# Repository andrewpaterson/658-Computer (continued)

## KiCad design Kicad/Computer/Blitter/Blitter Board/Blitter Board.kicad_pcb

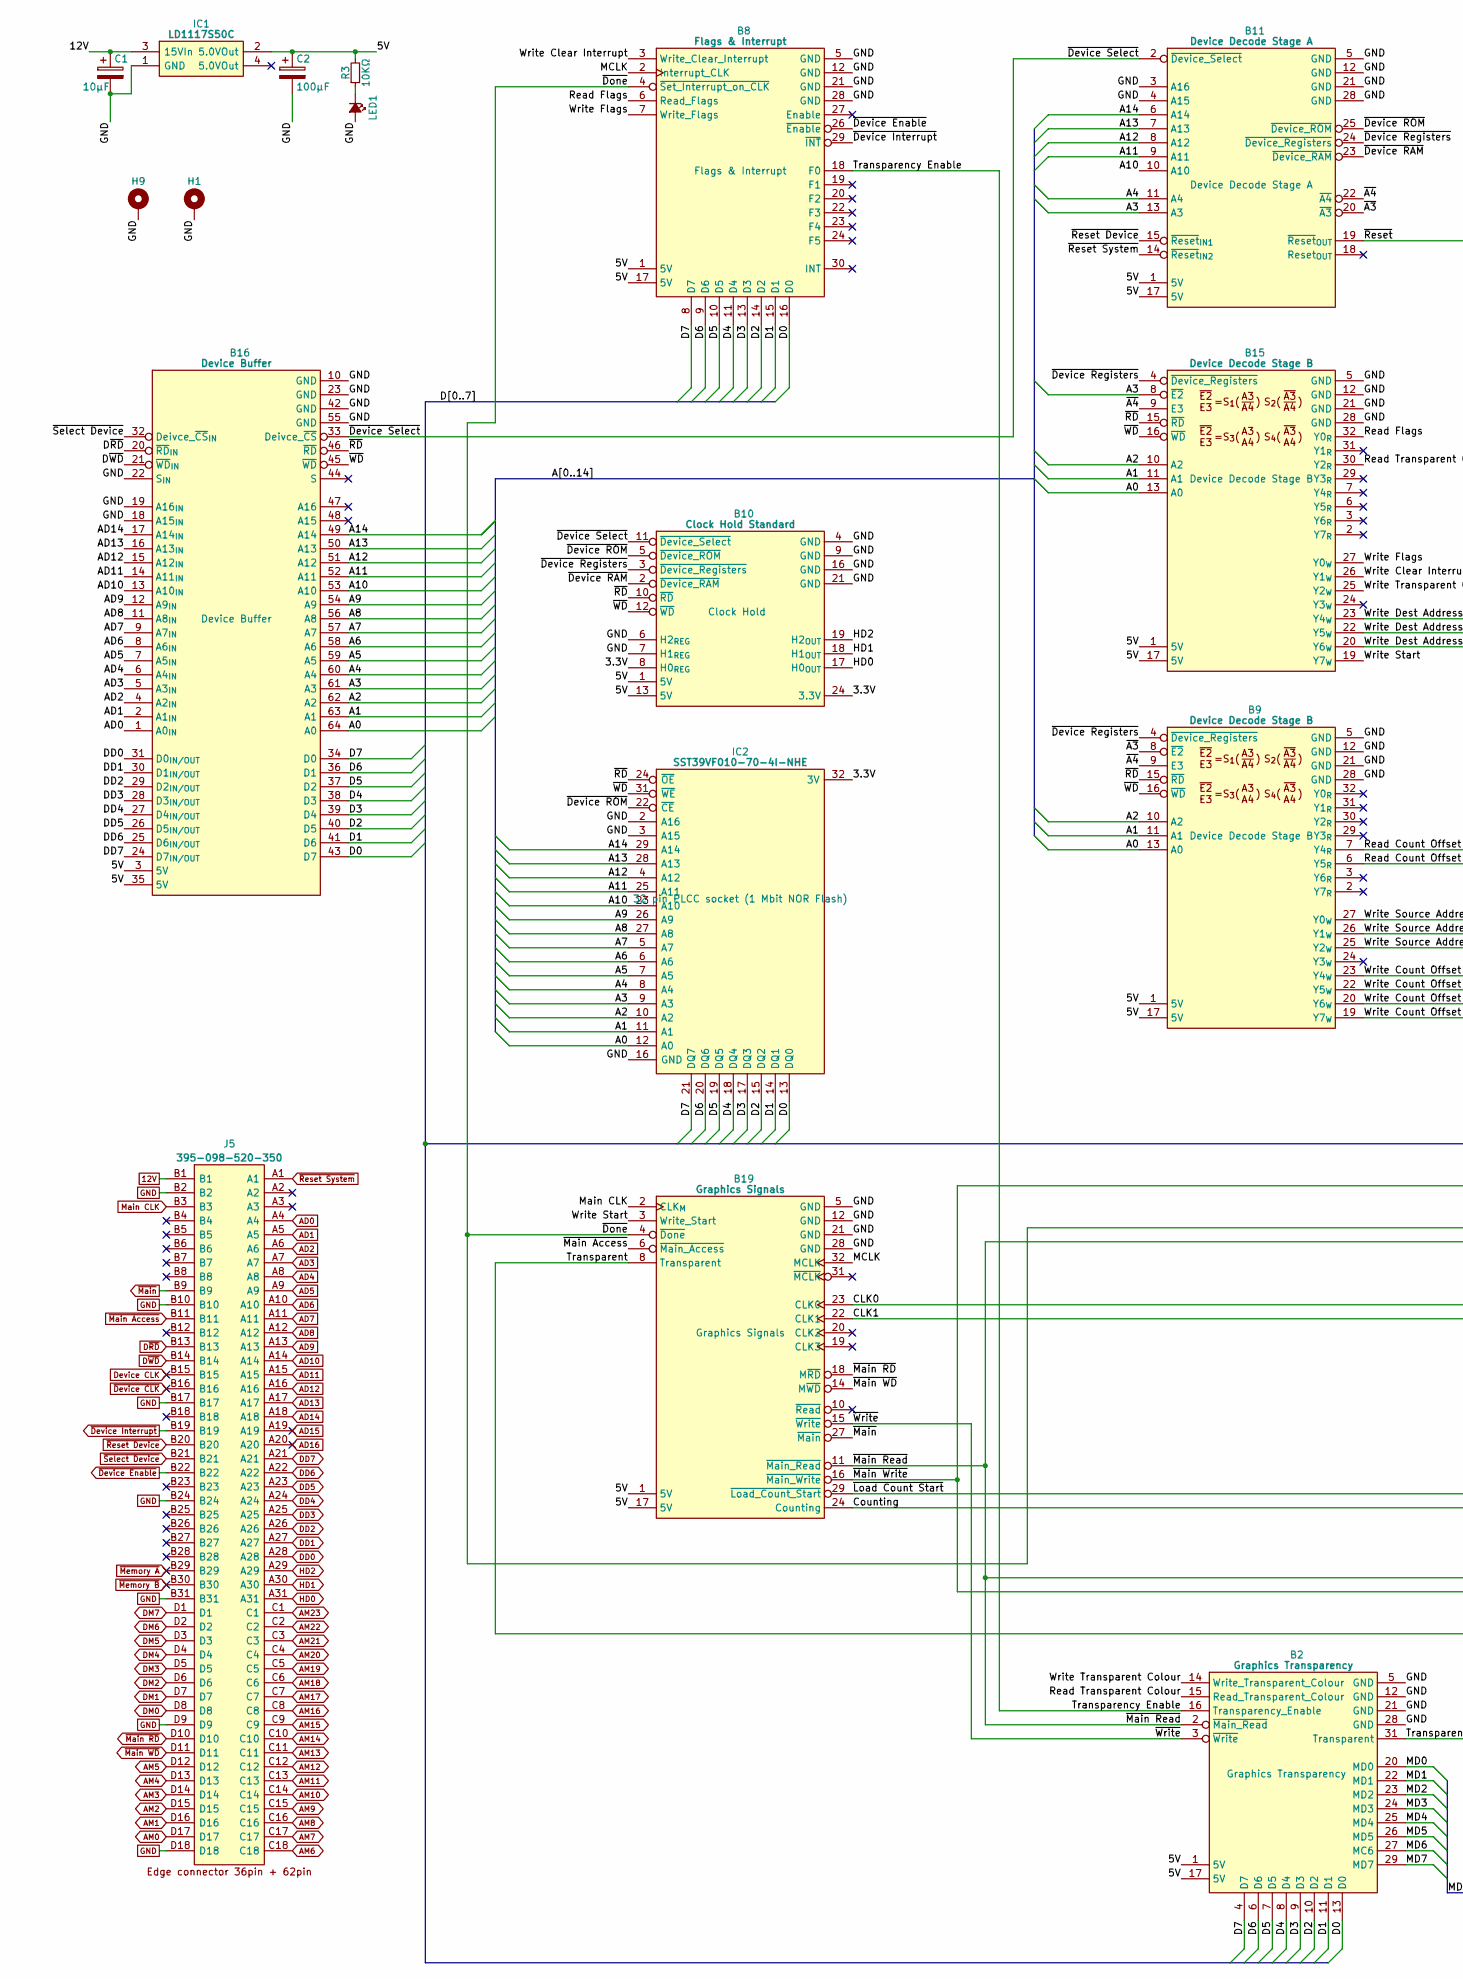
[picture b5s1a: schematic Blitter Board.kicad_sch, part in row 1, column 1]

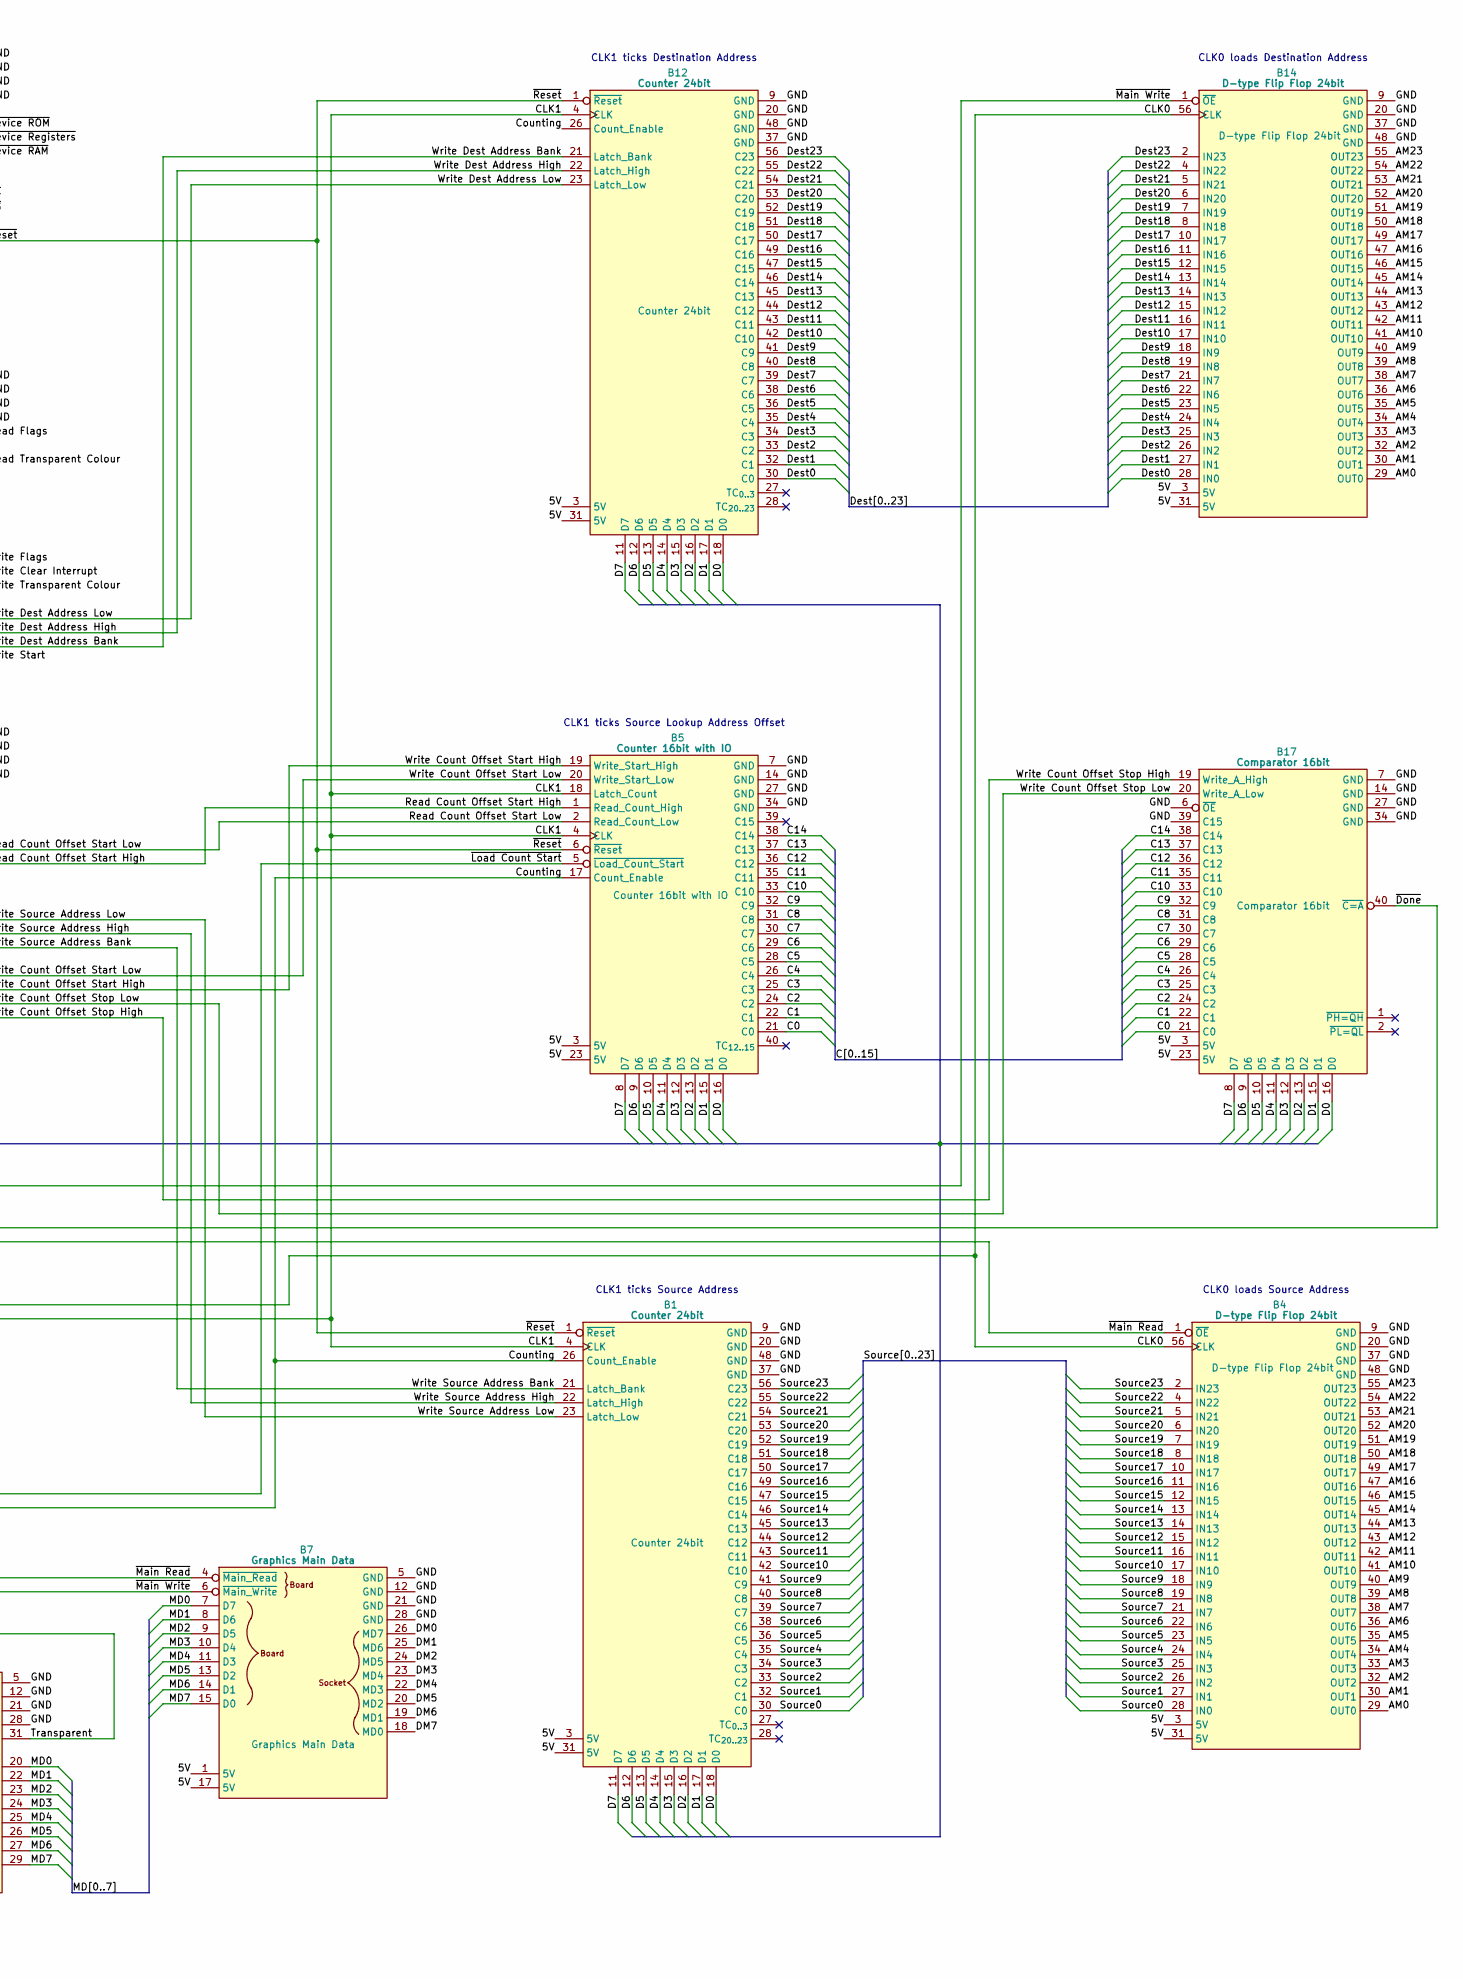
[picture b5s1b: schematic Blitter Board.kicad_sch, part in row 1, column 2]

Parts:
B1, B12: Counter 24bit; HCP65_Counter_24bit
B2: Graphics Transparency; HCP65_Graphics_Transparency
B4, B14: D-type Flip Flop 24bit; HCP65_D_Flip_Flop_24bit
B5: Counter 16bit with IO; HCP65_Counter_16bit_DIO
B7: Graphics Main Data; HCP65_Graphics_Main_Data
B8: Flags & Interrupt; HCP65_Flags_Interrupt
B9, B15: Device Decode Stage B; HCP65_Device_Decode_Stage_B
B10: Clock Hold Standard; HCP65_Clock_Hold_Standard
B11: Device Decode Stage A; HCP65_Device_Decode_Stage_A
B16: Device Buffer; HCP65_Device_Buffer
B17: Comparator 16bit; HCP65_Comparator_16bit
B19: Graphics Signals; HCP65_Graphics_Signals
C1: 10μF; CP_Radial_D4.0mm_P2.00mm
C2: 100μF; CP_Radial_D4.0mm_P2.00mm
H1, H9: MountingHole_Pad; HCP65_MountingHole_M3_
IC1: LD1117S50C; LD1117S33C; Manufacturer_Part_Number LD1117S50C
IC2: SST39VF010-70-4I-NHE; 5408803224008; Manufacturer_Part_Number SST39VF010-70-4I-NHE
J5: 395-098-520-350; 98pin Edge Connector; Manufacturer_Part_Number 395-098-520-350; Mouser Part Number 587-395-098-520-350
LED1: LED; LED_D5.0mm
R3: 10KΩ; R_0805

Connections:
12V: C1.1, IC1.3 (15VIn), J5.B1
/3.3V: B10.8 (H0_{REG}), B10.24 (3.3V), IC2.32 (3V)
/5V: B1.3 (5V), B1.31 (5V), B2.1 (5V), B2.17 (5V), B4.3 (5V), B4.31 (5V), B5.3 (5V), B5.23 (5V), B7.1 (5V), B7.17 (5V), B8.1 (5V), B8.17 (5V), B9.1 (5V), B9.17 (5V), B10.1 (5V), B10.13 (5V), B11.1 (5V), B11.17 (5V), B12.3 (5V), B12.31 (5V), B14.3 (5V), B14.31 (5V), B15.1 (5V), B15.17 (5V), B16.3 (5V), B16.35 (5V), B17.3 (5V), B17.23 (5V), B19.1 (5V), B19.17 (5V), C2.1, IC1.2 (5.0VOut), R3.2
/A0: B9.13 (A0), B15.13 (A0), B16.64 (A0), IC2.12 (A0)
/A1: B9.11 (A1), B15.11 (A1), B16.63 (A1), IC2.11 (A1)
/A2: B9.10 (A2), B15.10 (A2), B16.62 (A2), IC2.10 (A2)
/A3: B11.13 (A3), B15.8 (~E2), B16.61 (A3), IC2.9 (A3)
/A4: B11.11 (A4), B16.60 (A4), IC2.8 (A4)
/A5: B16.59 (A5), IC2.7 (A5)
/A6: B16.58 (A6), IC2.6 (A6)
/A7: B16.57 (A7), IC2.5 (A7)
/A8: B16.56 (A8), IC2.27 (A8)
/A9: B16.54 (A9), IC2.26 (A9)
/A10: B11.10 (A10), B16.53 (A10), IC2.23 (A10)
/A11: B11.9 (A11), B16.52 (A11), IC2.25 (A11)
/A12: B11.8 (A12), B16.51 (A12), IC2.4 (A12)
/A13: B11.7 (A13), B16.50 (A13), IC2.28 (A13)
/A14: B11.6 (A14), B16.49 (A14), IC2.29 (A14)
/C0: B5.21 (C0), B17.21 (C0)
/C1: B5.22 (C1), B17.22 (C1)
/C2: B5.24 (C2), B17.24 (C2)
/C3: B5.25 (C3), B17.25 (C3)
/C4: B5.26 (C4), B17.26 (C4)
/C5: B5.28 (C5), B17.28 (C5)
/C6: B5.29 (C6), B17.29 (C6)
/C7: B5.30 (C7), B17.30 (C7)
/C8: B5.31 (C8), B17.31 (C8)
/C9: B5.32 (C9), B17.32 (C9)
/C10: B5.33 (C10), B17.33 (C10)
/C11: B5.35 (C11), B17.35 (C11)
/C12: B5.36 (C12), B17.36 (C12)
/C13: B5.37 (C13), B17.37 (C13)
/C14: B5.38 (C14), B17.38 (C14)
/CLK0: B4.56 (CLK), B14.56 (CLK), B19.23 (CLK0)
/CLK1: B1.4 (CLK), B5.4 (CLK), B5.18 (Latch_Count), B12.4 (CLK), B19.22 (CLK1)
/Counting: B1.26 (Count_Enable), B5.17 (Count_Enable), B12.26 (Count_Enable), B19.24 (Counting)
/D0: B1.18 (D0), B2.13 (D0), B5.16 (D0), B8.16 (D0), B12.18 (D0), B16.43 (D7), B17.16 (D0), IC2.13 (DQ0)
/D1: B1.17 (D1), B2.11 (D1), B5.15 (D1), B8.15 (D1), B12.17 (D1), B16.41 (D6), B17.15 (D1), IC2.14 (DQ1)
/D2: B1.16 (D2), B2.10 (D2), B5.13 (D2), B8.14 (D2), B12.16 (D2), B16.40 (D5), B17.13 (D2), IC2.15 (DQ2)
/D3: B1.15 (D3), B2.9 (D3), B5.12 (D3), B8.13 (D3), B12.15 (D3), B16.39 (D4), B17.12 (D3), IC2.17 (DQ3)
/D4: B1.14 (D4), B2.8 (D4), B5.11 (D4), B8.11 (D4), B12.14 (D4), B16.38 (D3), B17.11 (D4), IC2.18 (DQ4)
/D5: B1.13 (D5), B2.7 (D5), B5.10 (D5), B8.10 (D5), B12.13 (D5), B16.37 (D2), B17.10 (D5), IC2.19 (DQ5)
/D6: B1.12 (D6), B2.6 (D6), B5.9 (D6), B8.9 (D6), B12.12 (D6), B16.36 (D1), B17.9 (D6), IC2.20 (DQ6)
/D7: B1.11 (D7), B2.4 (D7), B5.8 (D7), B8.8 (D7), B12.11 (D7), B16.34 (D0), B17.8 (D7), IC2.21 (DQ7)
/Dest0: B12.30 (C0), B14.28 (IN0)
/Dest1: B12.32 (C1), B14.27 (IN1)
/Dest2: B12.33 (C2), B14.26 (IN2)
/Dest3: B12.34 (C3), B14.25 (IN3)
/Dest4: B12.35 (C4), B14.24 (IN4)
/Dest5: B12.36 (C5), B14.23 (IN5)
/Dest6: B12.38 (C6), B14.22 (IN6)
/Dest7: B12.39 (C7), B14.21 (IN7)
/Dest8: B12.40 (C8), B14.19 (IN8)
/Dest9: B12.41 (C9), B14.18 (IN9)
/Dest10: B12.42 (C10), B14.17 (IN10)
/Dest11: B12.43 (C11), B14.16 (IN11)
/Dest12: B12.44 (C12), B14.15 (IN12)
/Dest13: B12.45 (C13), B14.14 (IN13)
/Dest14: B12.46 (C14), B14.13 (IN14)
/Dest15: B12.47 (C15), B14.12 (IN15)
/Dest16: B12.49 (C16), B14.11 (IN16)
/Dest17: B12.50 (C17), B14.10 (IN17)
/Dest18: B12.51 (C18), B14.8 (IN18)
/Dest19: B12.52 (C19), B14.7 (IN19)
/Dest20: B12.53 (C20), B14.6 (IN20)
/Dest21: B12.54 (C21), B14.5 (IN21)
/Dest22: B12.55 (C22), B14.4 (IN22)
/Dest23: B12.56 (C23), B14.2 (IN23)
/MCLK: B8.2 (Interrupt_CLK), B19.32 (MCLK)
/MD0: B2.20 (MD0), B7.7 (D7)
/MD1: B2.22 (MD1), B7.8 (D6)
/MD2: B2.23 (MD2), B7.9 (D5)
/MD3: B2.24 (MD3), B7.10 (D4)
/MD4: B2.25 (MD4), B7.11 (D3)
/MD5: B2.26 (MD5), B7.13 (D2)
/MD6: B2.27 (MC6), B7.14 (D1)
/MD7: B2.29 (MD7), B7.15 (D0)
/Read Count Offset Start High: B5.1 (Read_Count_High), B9.6 (Y5_{R})
/Read Count Offset Start Low: B5.2 (Read_Count_Low), B9.7 (Y4_{R})
/Read Flags: B8.6 (Read_Flags), B15.32 (Y0_{R})
/Read Transparent Colour: B2.15 (Read_Transparent_Colour), B15.30 (Y2_{R})
/Source0: B1.30 (C0), B4.28 (IN0)
/Source1: B1.32 (C1), B4.27 (IN1)
/Source2: B1.33 (C2), B4.26 (IN2)
/Source3: B1.34 (C3), B4.25 (IN3)
/Source4: B1.35 (C4), B4.24 (IN4)
/Source5: B1.36 (C5), B4.23 (IN5)
/Source6: B1.38 (C6), B4.22 (IN6)
/Source7: B1.39 (C7), B4.21 (IN7)
/Source8: B1.40 (C8), B4.19 (IN8)
/Source9: B1.41 (C9), B4.18 (IN9)
/Source10: B1.42 (C10), B4.17 (IN10)
/Source11: B1.43 (C11), B4.16 (IN11)
/Source12: B1.44 (C12), B4.15 (IN12)
/Source13: B1.45 (C13), B4.14 (IN13)
/Source14: B1.46 (C14), B4.13 (IN14)
/Source15: B1.47 (C15), B4.12 (IN15)
/Source16: B1.49 (C16), B4.11 (IN16)
/Source17: B1.50 (C17), B4.10 (IN17)
/Source18: B1.51 (C18), B4.8 (IN18)
/Source19: B1.52 (C19), B4.7 (IN19)
/Source20: B1.53 (C20), B4.6 (IN20)
/Source21: B1.54 (C21), B4.5 (IN21)
/Source22: B1.55 (C22), B4.4 (IN22)
/Source23: B1.56 (C23), B4.2 (IN23)
/Transparency Enable: B2.16 (Transparency_Enable), B8.18 (F0)
/Transparent: B2.31 (Transparent), B19.8 (Transparent)
/Write Clear Interrupt: B8.3 (Write_Clear_Interrupt), B15.26 (Y1_{W})
/Write Count Offset Start High: B5.19 (Write_Start_High), B9.22 (Y5_{W})
/Write Count Offset Start Low: B5.20 (Write_Start_Low), B9.23 (Y4_{W})
/Write Count Offset Stop High: B9.19 (Y7_{W}), B17.19 (Write_A_High)
/Write Count Offset Stop Low: B9.20 (Y6_{W}), B17.20 (Write_A_Low)
/Write Dest Address Bank: B12.21 (Latch_Bank), B15.20 (Y6_{W})
/Write Dest Address High: B12.22 (Latch_High), B15.22 (Y5_{W})
/Write Dest Address Low: B12.23 (Latch_Low), B15.23 (Y4_{W})
/Write Flags: B8.7 (Write_Flags), B15.27 (Y0_{W})
/Write Source Address Bank: B1.21 (Latch_Bank), B9.25 (Y2_{W})
/Write Source Address High: B1.22 (Latch_High), B9.26 (Y1_{W})
/Write Source Address Low: B1.23 (Latch_Low), B9.27 (Y0_{W})
/Write Start: B15.19 (Y7_{W}), B19.3 (Write_Start)
/Write Transparent Colour: B2.14 (Write_Transparent_Colour), B15.25 (Y2_{W})
/~A3: B9.8 (~E2), B11.20 (~A3)
/~A4: B9.9 (E3), B11.22 (~A4), B15.9 (E3)
/~Device RAM: B10.2 (~Device_RAM), B11.23 (~Device_RAM)
/~Device ROM: B10.5 (~Device_ROM), B11.25 (~Device_ROM), IC2.22 (~CE)
/~Device Registers: B9.4 (~Device_Registers), B10.3 (~Device_Registers), B11.24 (~Device_Registers), B15.4 (~Device_Registers)
/~Device Select: B10.11 (~Device_Select), B11.2 (~Device_Select), B16.33 (Deivce_~CS)
/~Done: B8.4 (~Set_Interrupt_on_CLK), B17.40 (~C=A), B19.4 (~Done)
/~Load Count Start: B5.5 (~Load_Count_Start), B19.29 (~Load_Count_Start)
/~Main Read: B2.2 (~Main_Read), B4.1 (~OE), B7.4 (~Main_Read), B19.11 (~Main_Read)
/~Main Write: B7.6 (~Main_Write), B14.1 (~OE), B19.16 (~Main_Write)
/~RD: B9.15 (~RD), B10.10 (~RD), B15.15 (~RD), B16.46 (~RD), IC2.24 (~OE)
/~Reset: B1.1 (~Reset), B5.6 (~Reset), B11.19 (~Reset_{OUT}), B12.1 (~Reset)
/~WD: B9.16 (~WD), B10.12 (~WD), B15.16 (~WD), B16.45 (~WD), IC2.31 (~WE)
/~Write: B2.3 (~Write), B19.15 (~Write)
AD0: B16.1 (A0_{IN}), J5.A4
AD1: B16.2 (A1_{IN}), J5.A5
AD2: B16.4 (A2_{IN}), J5.A6
AD3: B16.5 (A3_{IN}), J5.A7
AD4: B16.6 (A4_{IN}), J5.A8
AD5: B16.7 (A5_{IN}), J5.A9
AD6: B16.8 (A6_{IN}), J5.A10
AD7: B16.9 (A7_{IN}), J5.A11
AD8: B16.11 (A8_{IN}), J5.A12
AD9: B16.12 (A9_{IN}), J5.A13
AD10: B16.13 (A10_{IN}), J5.A14
AD11: B16.14 (A11_{IN}), J5.A15
AD12: B16.15 (A12_{IN}), J5.A16
AD13: B16.16 (A13_{IN}), J5.A17
AD14: B16.17 (A14_{IN}), J5.A18
AD15: J5.A19
AD16: J5.A20
AM0: B4.29 (OUT0), B14.29 (OUT0), J5.D17
AM1: B4.30 (OUT1), B14.30 (OUT1), J5.D16
AM2: B4.32 (OUT2), B14.32 (OUT2), J5.D15
AM3: B4.33 (OUT3), B14.33 (OUT3), J5.D14
AM4: B4.34 (OUT4), B14.34 (OUT4), J5.D13
AM5: B4.35 (OUT5), B14.35 (OUT5), J5.D12
AM6: B4.36 (OUT6), B14.36 (OUT6), J5.C18
AM7: B4.38 (OUT7), B14.38 (OUT7), J5.C17
AM8: B4.39 (OUT8), B14.39 (OUT8), J5.C16
AM9: B4.40 (OUT9), B14.40 (OUT9), J5.C15
AM10: B4.41 (OUT10), B14.41 (OUT10), J5.C14
AM11: B4.42 (OUT11), B14.42 (OUT11), J5.C13
AM12: B4.43 (OUT12), B14.43 (OUT12), J5.C12
AM13: B4.44 (OUT13), B14.44 (OUT13), J5.C11
AM14: B4.45 (OUT14), B14.45 (OUT14), J5.C10
AM15: B4.46 (OUT15), B14.46 (OUT15), J5.C9
AM16: B4.47 (OUT16), B14.47 (OUT16), J5.C8
AM17: B4.49 (OUT17), B14.49 (OUT17), J5.C7
AM18: B4.50 (OUT18), B14.50 (OUT18), J5.C6
AM19: B4.51 (OUT19), B14.51 (OUT19), J5.C5
AM20: B4.52 (OUT20), B14.52 (OUT20), J5.C4
AM21: B4.53 (OUT21), B14.53 (OUT21), J5.C3
AM22: B4.54 (OUT22), B14.54 (OUT22), J5.C2
AM23: B4.55 (OUT23), B14.55 (OUT23), J5.C1
DD0: B16.31 (D0_{IN/OUT}), J5.A28
DD1: B16.30 (D1_{IN/OUT}), J5.A27
DD2: B16.29 (D2_{IN/OUT}), J5.A26
DD3: B16.28 (D3_{IN/OUT}), J5.A25
DD4: B16.27 (D4_{IN/OUT}), J5.A24
DD5: B16.26 (D5_{IN/OUT}), J5.A23
DD6: B16.25 (D6_{IN/OUT}), J5.A22
DD7: B16.24 (D7_{IN/OUT}), J5.A21
DM0: B7.26 (MD7), J5.D8
DM1: B7.25 (MD6), J5.D7
DM2: B7.24 (MD5), J5.D6
DM3: B7.23 (MD4), J5.D5
DM4: B7.22 (MD3), J5.D4
DM5: B7.20 (MD2), J5.D3
DM6: B7.19 (MD1), J5.D2
DM7: B7.18 (MD0), J5.D1
Device CLK: J5.B15
D~RD: B16.20 (~RD_{IN}), J5.B13
D~WD: B16.21 (~WD_{IN}), J5.B14
GND: B1.9 (GND), B1.20 (GND), B1.37 (GND), B1.48 (GND), B2.5 (GND), B2.12 (GND), B2.21 (GND), B2.28 (GND), B4.9 (GND), B4.20 (GND), B4.37 (GND), B4.48 (GND), B5.7 (GND), B5.14 (GND), B5.27 (GND), B5.34 (GND), B7.5 (GND), B7.12 (GND), B7.21 (GND), B7.28 (GND), B8.5 (GND), B8.12 (GND), B8.21 (GND), B8.28 (GND), B9.5 (GND), B9.12 (GND), B9.21 (GND), B9.28 (GND), B10.4 (GND), B10.6 (H2_{REG}), B10.7 (H1_{REG}), B10.9 (GND), B10.16 (GND), B10.21 (GND), B11.3 (A16), B11.4 (A15), B11.5 (GND), B11.12 (GND), B11.21 (GND), B11.28 (GND), B12.9 (GND), B12.20 (GND), B12.37 (GND), B12.48 (GND), B14.9 (GND), B14.20 (GND), B14.37 (GND), B14.48 (GND), B15.5 (GND), B15.12 (GND), B15.21 (GND), B15.28 (GND), B16.10 (GND), B16.18 (A15_{IN}), B16.19 (A16_{IN}), B16.22 (S_{IN}), B16.23 (GND), B16.42 (GND), B16.55 (GND), B17.6 (~OE), B17.7 (GND), B17.14 (GND), B17.27 (GND), B17.34 (GND), B17.39 (C15), B19.5 (GND), B19.12 (GND), B19.21 (GND), B19.28 (GND), C1.2, C2.2, H1.1 (GND), H9.1 (GND), IC1.1 (GND), IC2.2 (A16), IC2.3 (A15), IC2.16 (GND), J5.B2, J5.B10, J5.B17, J5.B24, J5.B31, J5.D9, J5.D18, LED1.2 (A)
HD0: B10.17 (H0_{OUT}), J5.A31
HD1: B10.18 (H1_{OUT}), J5.A30
HD2: B10.19 (H2_{OUT}), J5.A29
Main CLK: B19.2 (CLK_{M}), J5.B3
unnamed: LED1.1 (K), R3.1
~Device CLK: J5.B16
~Device Enable: B8.26 (~Enable), J5.B22
~Device Interrupt: B8.29 (~INT), J5.B19
~Main Access: B19.6 (~Main_Access), J5.B11
~Main RD: B19.18 (M~RD), J5.D10
~Main WD: B19.14 (M~WD), J5.D11
~Main: B19.27 (~Main), J5.B9
~Memory A: J5.B29
~Memory B: J5.B30
~Reset Device: B11.15 (~Reset_{IN1}), J5.B20
~Reset System: B11.14 (~Reset_{IN2}), J5.A1
~Select Device: B16.32 (Deivce_~CS_{IN}), J5.B21

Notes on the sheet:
CLK1 ticks Source Lookup Address Offset
CLK0 loads Destination Address
CLK1 ticks Destination Address
CLK1 ticks Source Address
CLK0 loads Source Address

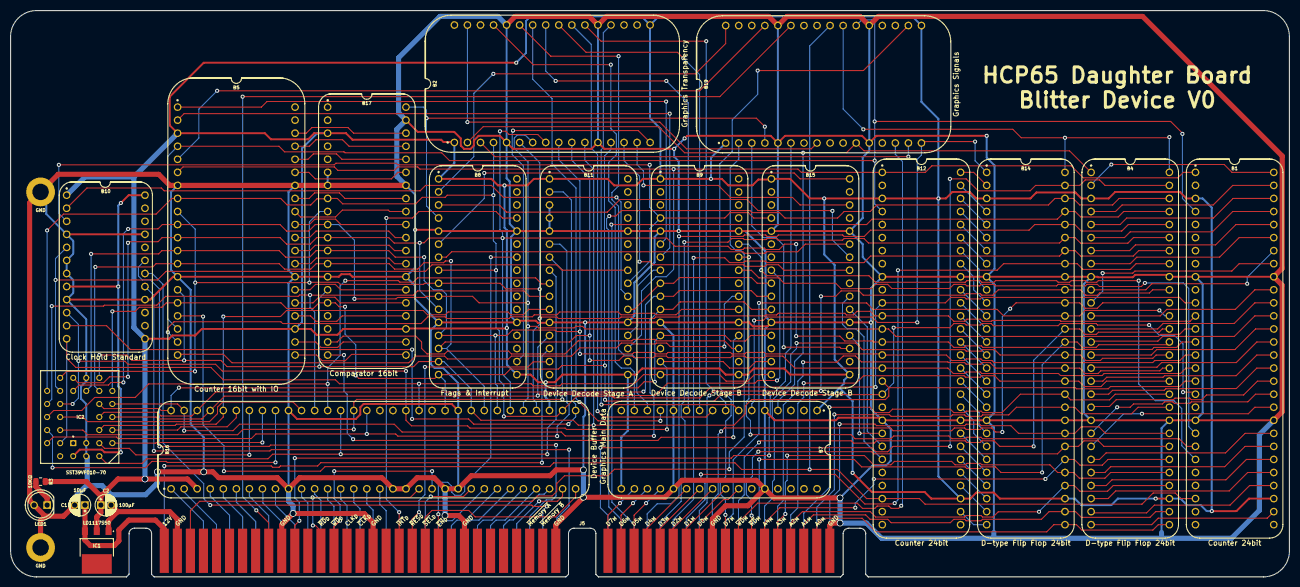
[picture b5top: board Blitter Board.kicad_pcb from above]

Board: 2 copper layers, 248.9 x 110.2 mm, 24 parts (0 on the bottom side), 207 nets.

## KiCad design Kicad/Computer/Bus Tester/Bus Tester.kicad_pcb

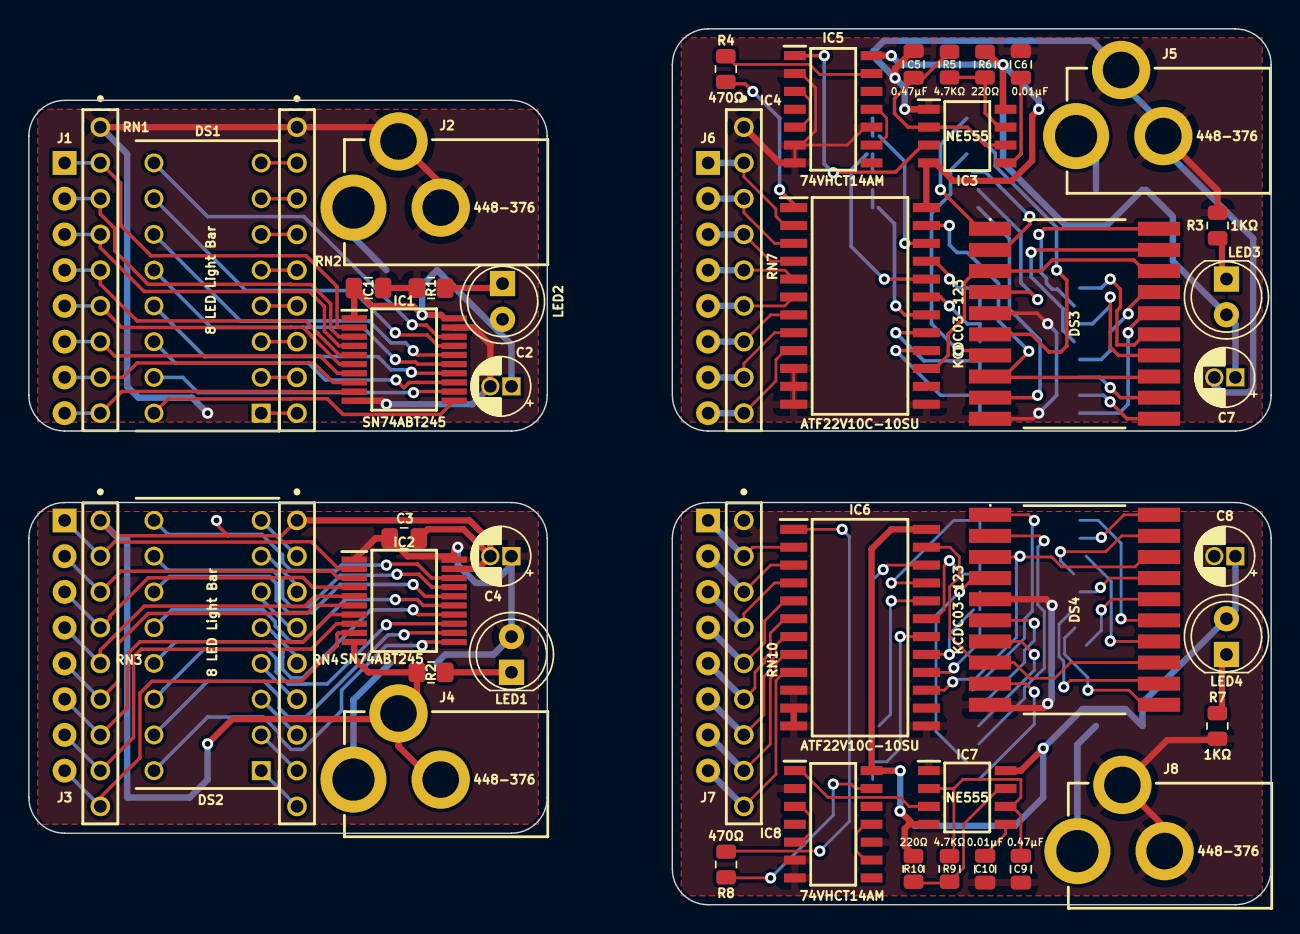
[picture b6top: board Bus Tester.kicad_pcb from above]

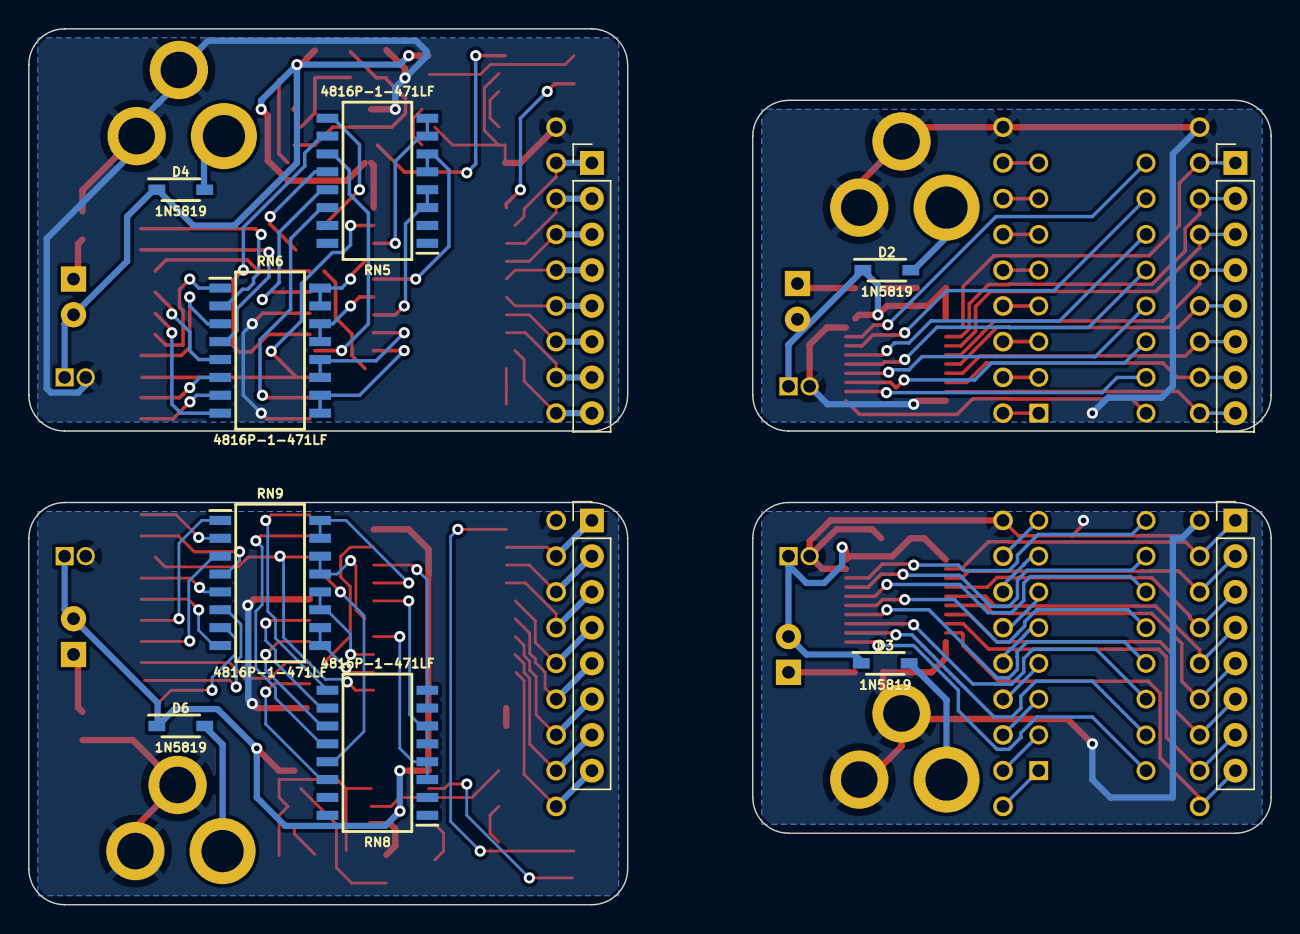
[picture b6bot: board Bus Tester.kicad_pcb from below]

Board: 2 copper layers, 88.3 x 62.2 mm, 58 parts (12 on the bottom side), 142 nets.

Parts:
C1, C3: C_Small; C_0805_2012Metric_Pad1.18x1.45mm_HandSolder
C2, C4, C7, C8: C_Polarized; CP_Radial_D4.0mm_P1.50mm
C5, C6, C9, C10: C_0805
D2, D3, D4, D6: 1N5819HW-7-F; SOD3716X145N
DS1, DS2: 8 LED Light Bar; DIP8LEDBAR
DS3, DS4: KCDC03-123; KCDC03123
IC1, IC2: SN74ABT245; SOP65P780X200-20N
IC3, IC7: NE555DRG4; SOIC127P600X175-8N
IC4, IC6: ATF22V10C-10SU; SOIC127P1032X265-24N
IC5, IC8: 74VHCT14AM; SOIC127P600X175-14N
J1, J3, J6, J7: Conn_01x08_Male; PinHeader_1x08_P2.54mm_Vertical
J2, J4, J5, J8: 448-376; 448376
LED1, LED2, LED3, LED4: LED_Small_Filled; LED_D5.0mm
R1, R2: R_Small; R_0805_2012Metric_Pad1.20x1.40mm_HandSolder
R3, R4, R5, R6, R7, R8, R9, R10: R_0805
RN1, RN3, RN7, RN10: 4609X-101-105LF; 4609X
RN2, RN4: 4609X-101-102LF; 4609X
RN5, RN6, RN8, RN9: 4816P-1-471LF; SOIC127P762X215-16N

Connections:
/Left Handed Bus 7-Segment/5V: C7.1, D4.1, IC3.4 (RESET), IC3.8 (VCC), IC4.24 (5V), IC5.14 (5V), LED3.2 (A), R6.2
/Left Handed Bus 7-Segment/A Seg: IC4.17 (I/O3), RN6.11, RN6.12
/Left Handed Bus 7-Segment/AA: IC4.2 (IN0), J6.1, RN7.2 (R1)
/Left Handed Bus 7-Segment/AB: IC4.3 (IN1), J6.2, RN7.3 (R2)
/Left Handed Bus 7-Segment/AC: IC4.4 (IN2/PD), J6.3, RN7.4 (R3)
/Left Handed Bus 7-Segment/AD: IC4.5 (IN3), J6.4, RN7.5 (R4)
/Left Handed Bus 7-Segment/B Seg: IC4.16 (I/O2), RN6.9, RN6.10
/Left Handed Bus 7-Segment/BA: IC4.6 (IN4), J6.5, RN7.6 (R5)
/Left Handed Bus 7-Segment/BB: IC4.7 (IN5), J6.6, RN7.7 (R6)
/Left Handed Bus 7-Segment/BC: IC4.8 (IN6), J6.7, RN7.8 (R7)
/Left Handed Bus 7-Segment/BD: IC4.9 (IN7), J6.8, RN7.9 (R8)
/Left Handed Bus 7-Segment/C Seg: IC4.18 (I/O4), RN5.3, RN5.4
/Left Handed Bus 7-Segment/Cathode Left: DS3.3 (Cathode_{(Left)}), DS3.18 (Cathode_{(Left)}), IC4.15 (I/O1)
/Left Handed Bus 7-Segment/Cathode Right: DS3.8 (Cathode_{(Right)}), DS3.13 (Cathode_{(Right)}), IC4.23 (I/O9)
/Left Handed Bus 7-Segment/Clock: IC4.1 (CLK/IN), R4.1
/Left Handed Bus 7-Segment/D Seg: IC4.20 (I/O6), RN5.5, RN5.6
/Left Handed Bus 7-Segment/E Seg: IC4.22 (I/O8), RN5.7, RN5.8
/Left Handed Bus 7-Segment/F Seg: IC4.19 (I/O5), RN6.13, RN6.14
/Left Handed Bus 7-Segment/G Seg: IC4.21 (I/O7), RN6.15, RN6.16
/Left Handed Bus 7-Segment/GND: C5.2, C6.2, C7.2, DS3.5 (Dot_{(Left)}), DS3.10 (Dot_{(Right)}), IC3.1 (GND), IC4.10 (IN8), IC4.11 (IN9), IC4.12 (GND), IC4.13 (IN10), IC5.2 (1Y), IC5.6 (3Y), IC5.7 (GND), IC5.10 (5Y), J5.B1 (GND1), J5.C1 (GND2), R3.1, RN7.1 (PC)
/Left Handed Bus LED/5V: C1.2, C2.1, D2.1, IC1.1 (DIR), IC1.20 (5V), LED2.2 (A)
/Left Handed Bus LED/GND: C1.1, C2.2, IC1.10 (GND), IC1.19 (~OE), J2.B1 (GND1), J2.C1 (GND2), R1.2, RN1.1 (PC), RN2.1 (PC)
/Right Handed Bus 7-Segment/5V: C8.1, D6.1, IC6.24 (5V), IC7.4 (RESET), IC7.8 (VCC), IC8.14 (5V), LED4.2 (A), R10.2
/Right Handed Bus 7-Segment/A Seg: IC6.17 (I/O3), RN9.11, RN9.12
/Right Handed Bus 7-Segment/AA: IC6.2 (IN0), J7.1, RN10.2 (R1)
/Right Handed Bus 7-Segment/AB: IC6.3 (IN1), J7.2, RN10.3 (R2)
/Right Handed Bus 7-Segment/AC: IC6.4 (IN2/PD), J7.3, RN10.4 (R3)
/Right Handed Bus 7-Segment/AD: IC6.5 (IN3), J7.4, RN10.5 (R4)
/Right Handed Bus 7-Segment/B Seg: IC6.16 (I/O2), RN9.9, RN9.10
/Right Handed Bus 7-Segment/BA: IC6.6 (IN4), J7.5, RN10.6 (R5)
/Right Handed Bus 7-Segment/BB: IC6.7 (IN5), J7.6, RN10.7 (R6)
/Right Handed Bus 7-Segment/BC: IC6.8 (IN6), J7.7, RN10.8 (R7)
/Right Handed Bus 7-Segment/BD: IC6.9 (IN7), J7.8, RN10.9 (R8)
/Right Handed Bus 7-Segment/C Seg: IC6.18 (I/O4), RN8.3, RN8.4
/Right Handed Bus 7-Segment/Cathode Left: DS4.3 (Cathode_{(Left)}), DS4.18 (Cathode_{(Left)}), IC6.15 (I/O1)
/Right Handed Bus 7-Segment/Cathode Right: DS4.8 (Cathode_{(Right)}), DS4.13 (Cathode_{(Right)}), IC6.23 (I/O9)
/Right Handed Bus 7-Segment/Clock: IC6.1 (CLK/IN), R8.1
/Right Handed Bus 7-Segment/D Seg: IC6.20 (I/O6), RN8.5, RN8.6
/Right Handed Bus 7-Segment/E Seg: IC6.22 (I/O8), RN8.7, RN8.8
/Right Handed Bus 7-Segment/F Seg: IC6.19 (I/O5), RN9.13, RN9.14
/Right Handed Bus 7-Segment/G Seg: IC6.21 (I/O7), RN9.15, RN9.16
/Right Handed Bus 7-Segment/GND: C8.2, C9.2, C10.2, DS4.5 (Dot_{(Left)}), DS4.10 (Dot_{(Right)}), IC6.10 (IN8), IC6.11 (IN9), IC6.12 (GND), IC6.13 (IN10), IC7.1 (GND), IC8.2 (1Y), IC8.6 (3Y), IC8.7 (GND), IC8.10 (5Y), J8.B1 (GND1), J8.C1 (GND2), R7.1, RN10.1 (PC)
/Right Handed Bus LED/5V: C3.2, C4.1, D3.1, IC2.1 (DIR), IC2.20 (5V), LED1.2 (A)
/Right Handed Bus LED/GND: C3.1, C4.2, IC2.10 (GND), IC2.19 (~OE), J4.B1 (GND1), J4.C1 (GND2), R2.2, RN3.1 (PC), RN4.1 (PC)
unnamed: D2.2, J2.A1 (VCC)
unnamed: D3.2, J4.A1 (VCC)
unnamed: D4.2, J5.A1 (VCC)
unnamed: D6.2, J8.A1 (VCC)
unnamed: DS1.1 (ANODE_A), RN2.9 (R8)
unnamed: DS1.2 (ANODE_B), RN2.8 (R7)
unnamed: DS1.3 (ANODE_C), RN2.7 (R6)
unnamed: DS1.4 (ANODE_D), RN2.6 (R5)
unnamed: DS1.5 (ANODE_E), RN2.5 (R4)
unnamed: DS1.6 (ANODE_F), RN2.4 (R3)
unnamed: DS1.7 (ANODE_G), RN2.3 (R2)
unnamed: DS1.8 (ANODE_H), RN2.2 (R1)
unnamed: DS1.9 (CATHODE_H), IC1.18 (B1)
unnamed: DS1.10 (CATHODE_G), IC1.17 (B2)
unnamed: DS1.11 (CATHODE_F), IC1.16 (B3)
unnamed: DS1.12 (CATHODE_E), IC1.15 (B4)
unnamed: DS1.13 (CATHODE_D), IC1.14 (B5)
unnamed: DS1.14 (CATHODE_C), IC1.13 (B6)
unnamed: DS1.15 (CATHODE_B), IC1.12 (B7)
unnamed: DS1.16 (CATHODE_A), IC1.11 (B8)
unnamed: DS2.1 (ANODE_A), RN4.9 (R8)
unnamed: DS2.2 (ANODE_B), RN4.8 (R7)
unnamed: DS2.3 (ANODE_C), RN4.7 (R6)
unnamed: DS2.4 (ANODE_D), RN4.6 (R5)
unnamed: DS2.5 (ANODE_E), RN4.5 (R4)
unnamed: DS2.6 (ANODE_F), RN4.4 (R3)
unnamed: DS2.7 (ANODE_G), RN4.3 (R2)
unnamed: DS2.8 (ANODE_H), RN4.2 (R1)
unnamed: DS2.9 (CATHODE_H), IC2.18 (B1)
unnamed: DS2.10 (CATHODE_G), IC2.17 (B2)
unnamed: DS2.11 (CATHODE_F), IC2.16 (B3)
unnamed: DS2.12 (CATHODE_E), IC2.15 (B4)
unnamed: DS2.13 (CATHODE_D), IC2.14 (B5)
unnamed: DS2.14 (CATHODE_C), IC2.13 (B6)
unnamed: DS2.15 (CATHODE_B), IC2.12 (B7)
unnamed: DS2.16 (CATHODE_A), IC2.11 (B8)
unnamed: DS3.1 (E-Seg_{(Left)}), RN5.9
unnamed: DS3.2 (D-Seg_{(Left)}), RN5.12
unnamed: DS3.4 (C-Seg_{(Left)}), RN5.13
unnamed: DS3.6 (E-Seg_{(Right)}), RN5.10
unnamed: DS3.7 (D-Seg_{(Right)}), RN5.11
unnamed: DS3.9 (C-Seg_{(Right)}), RN5.14
unnamed: DS3.11 (B-Seg_{(Right)}), RN6.7
unnamed: DS3.12 (A-Seg_{(Right)}), RN6.6
unnamed: DS3.14 (F-Seg_{(Right)}), RN6.3
unnamed: DS3.15 (G-Seg_{(Right)}), RN6.1
unnamed: DS3.16 (B-Seg_{(Left)}), RN6.8
unnamed: DS3.17 (A-Seg_{(Left)}), RN6.5
unnamed: DS3.19 (F-Seg_{(Left)}), RN6.4
unnamed: DS3.20 (G-Seg_{(Left)}), RN6.2
unnamed: DS4.1 (E-Seg_{(Left)}), RN8.9
unnamed: DS4.2 (D-Seg_{(Left)}), RN8.12
unnamed: DS4.4 (C-Seg_{(Left)}), RN8.13
unnamed: DS4.6 (E-Seg_{(Right)}), RN8.10
unnamed: DS4.7 (D-Seg_{(Right)}), RN8.11
unnamed: DS4.9 (C-Seg_{(Right)}), RN8.14
unnamed: DS4.11 (B-Seg_{(Right)}), RN9.7
unnamed: DS4.12 (A-Seg_{(Right)}), RN9.6
unnamed: DS4.14 (F-Seg_{(Right)}), RN9.3
unnamed: DS4.15 (G-Seg_{(Right)}), RN9.1
unnamed: DS4.16 (B-Seg_{(Left)}), RN9.8
unnamed: DS4.17 (A-Seg_{(Left)}), RN9.5
unnamed: DS4.19 (F-Seg_{(Left)}), RN9.4
unnamed: DS4.20 (G-Seg_{(Left)}), RN9.2
unnamed: IC1.2 (A1), J1.1, RN1.2 (R1)
unnamed: IC1.3 (A2), J1.2, RN1.3 (R2)
unnamed: IC1.4 (A3), J1.3, RN1.4 (R3)
unnamed: IC1.5 (A4), J1.4, RN1.5 (R4)
unnamed: IC1.6 (A5), J1.5, RN1.6 (R5)
unnamed: IC1.7 (A6), J1.6, RN1.7 (R6)
unnamed: IC1.8 (A7), J1.7, RN1.8 (R7)
unnamed: IC1.9 (A8), J1.8, RN1.9 (R8)
unnamed: IC2.2 (A1), J3.1, RN3.2 (R1)
unnamed: IC2.3 (A2), J3.2, RN3.3 (R2)
unnamed: IC2.4 (A3), J3.3, RN3.4 (R3)
unnamed: IC2.5 (A4), J3.4, RN3.5 (R4)
unnamed: IC2.6 (A5), J3.5, RN3.6 (R5)
unnamed: IC2.7 (A6), J3.6, RN3.7 (R6)
unnamed: IC2.8 (A7), J3.7, RN3.8 (R7)
unnamed: IC2.9 (A8), J3.8, RN3.9 (R8)
unnamed: C5.1, IC3.2 (TRIG), IC3.6 (THRES), R5.1
unnamed: IC3.3 (OUT), IC5.1 (1A)
unnamed: C6.1, IC3.5 (CONT)
unnamed: IC3.7 (DISCH), R5.2, R6.1
unnamed: IC5.3 (2A), IC5.5 (3A)
unnamed: IC5.9 (4A), IC5.11 (5A)
unnamed: IC5.13 (6A), R4.2
unnamed: C9.1, IC7.2 (TRIG), IC7.6 (THRES), R9.1
unnamed: IC7.3 (OUT), IC8.1 (1A)
unnamed: C10.1, IC7.5 (CONT)
unnamed: IC7.7 (DISCH), R9.2, R10.1
unnamed: IC8.3 (2A), IC8.5 (3A)
unnamed: IC8.9 (4A), IC8.11 (5A)
unnamed: IC8.13 (6A), R8.2
unnamed: LED1.1 (K), R2.1
unnamed: LED2.1 (K), R1.1
unnamed: LED3.1 (K), R3.2
unnamed: LED4.1 (K), R7.2
